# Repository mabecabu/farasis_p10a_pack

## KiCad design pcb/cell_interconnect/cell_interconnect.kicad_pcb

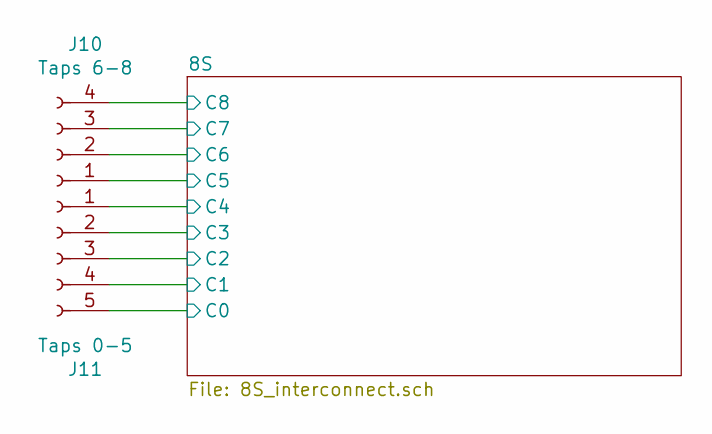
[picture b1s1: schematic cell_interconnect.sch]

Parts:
J10: Taps 6-8; PinSocket_1x04_P2.54mm_Vertical
J11: Taps 0-5; PinSocket_1x05_P2.54mm_Vertical

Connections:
/8S/C0: J11.5; also elsewhere on the board
/8S/C1: J11.4; also elsewhere on the board
/8S/C2: J11.3; also elsewhere on the board
/8S/C3: J11.2; also elsewhere on the board
/8S/C4: J11.1; also elsewhere on the board
/8S/C5: J10.1; also elsewhere on the board
/8S/C6: J10.2; also elsewhere on the board
/8S/C7: J10.3; also elsewhere on the board
/8S/C8: J10.4; also elsewhere on the board

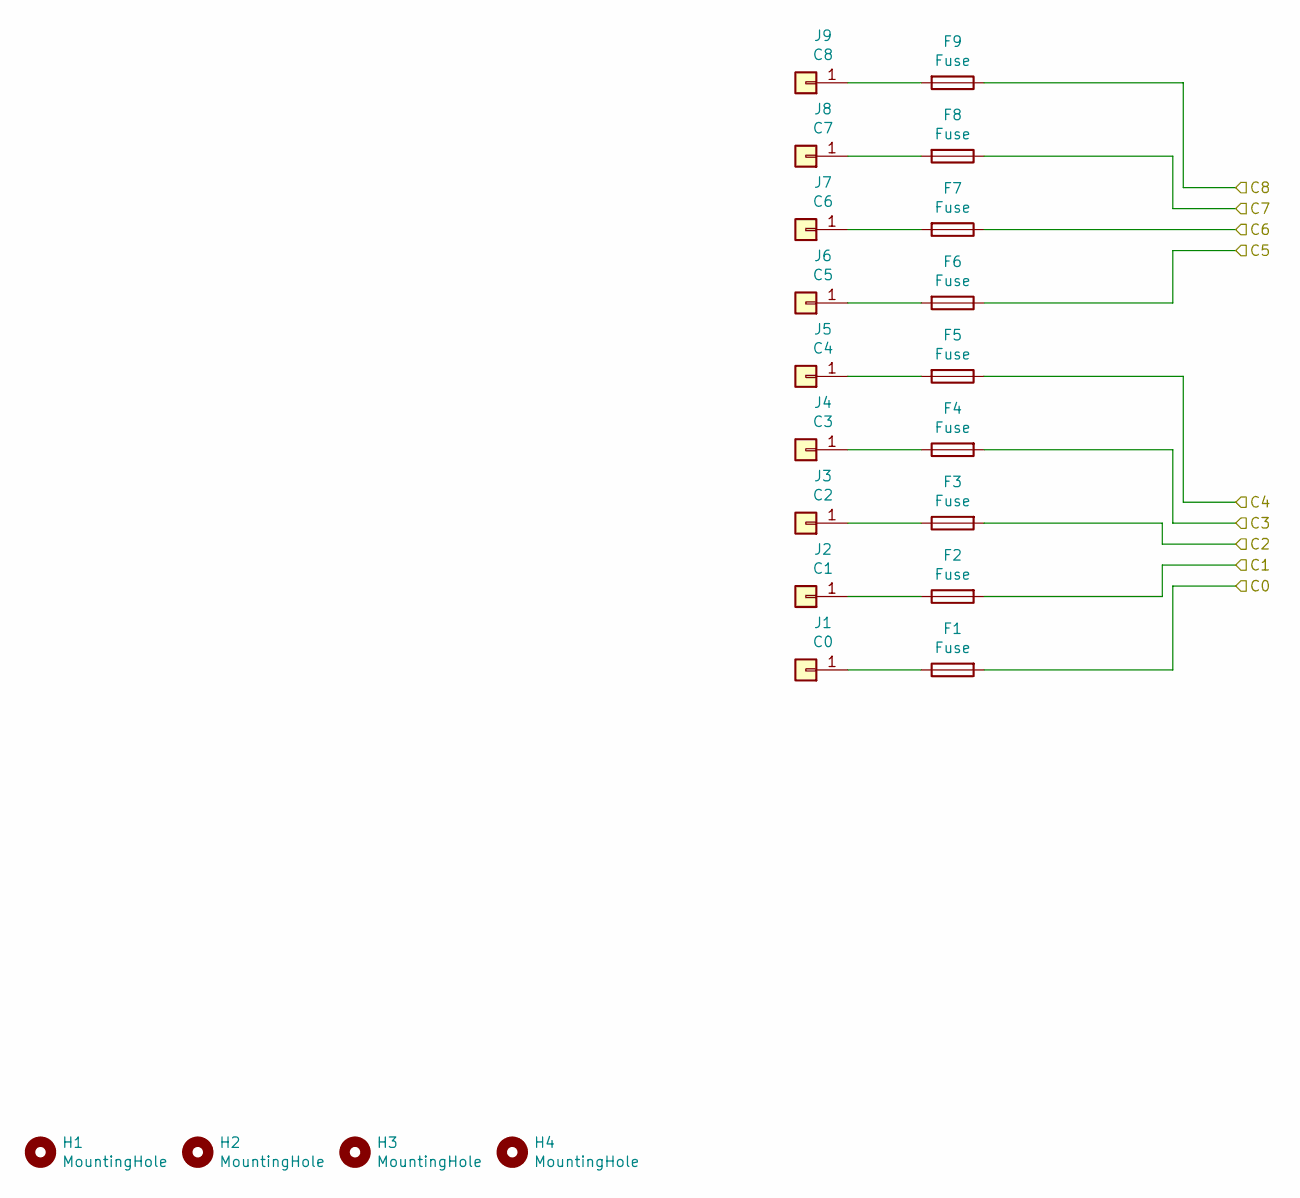
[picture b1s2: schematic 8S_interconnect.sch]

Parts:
F1, F2, F3, F4, F5, F6, F7, F9: Fuse; R_0603_1608Metric
F8: Fuse; R_0603_1608Metric; MPN C2Q 300
H1, H2, H3, H4: MountingHole; MountingHole_3.2mm_M3
J1: C0; farasis_p10a_end_tab_offset_right
J2: C1; farasis_p10a_tab
J3: C2; farasis_p10a_tab
J4: C3; farasis_p10a_tab
J5: C4; farasis_p10a_tab
J6: C5; farasis_p10a_tab
J7: C6; farasis_p10a_tab
J8: C7; farasis_p10a_tab
J9: C8; farasis_p10a_end_tab_offset_left

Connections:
/8S/C0: F1.2; also elsewhere on the board
/8S/C1: F2.2; also elsewhere on the board
/8S/C2: F3.2; also elsewhere on the board
/8S/C3: F4.2; also elsewhere on the board
/8S/C4: F5.1; also elsewhere on the board
/8S/C5: F6.1; also elsewhere on the board
/8S/C6: F7.1; also elsewhere on the board
/8S/C7: F8.1; also elsewhere on the board
/8S/C8: F9.1; also elsewhere on the board
unnamed: F1.1, J1.1
unnamed: F2.1, J2.1
unnamed: F3.1, J3.1
unnamed: F4.1, J4.1
unnamed: F5.2, J5.1
unnamed: F6.2, J6.1
unnamed: F7.2, J7.1
unnamed: F8.2, J8.1
unnamed: F9.2, J9.1

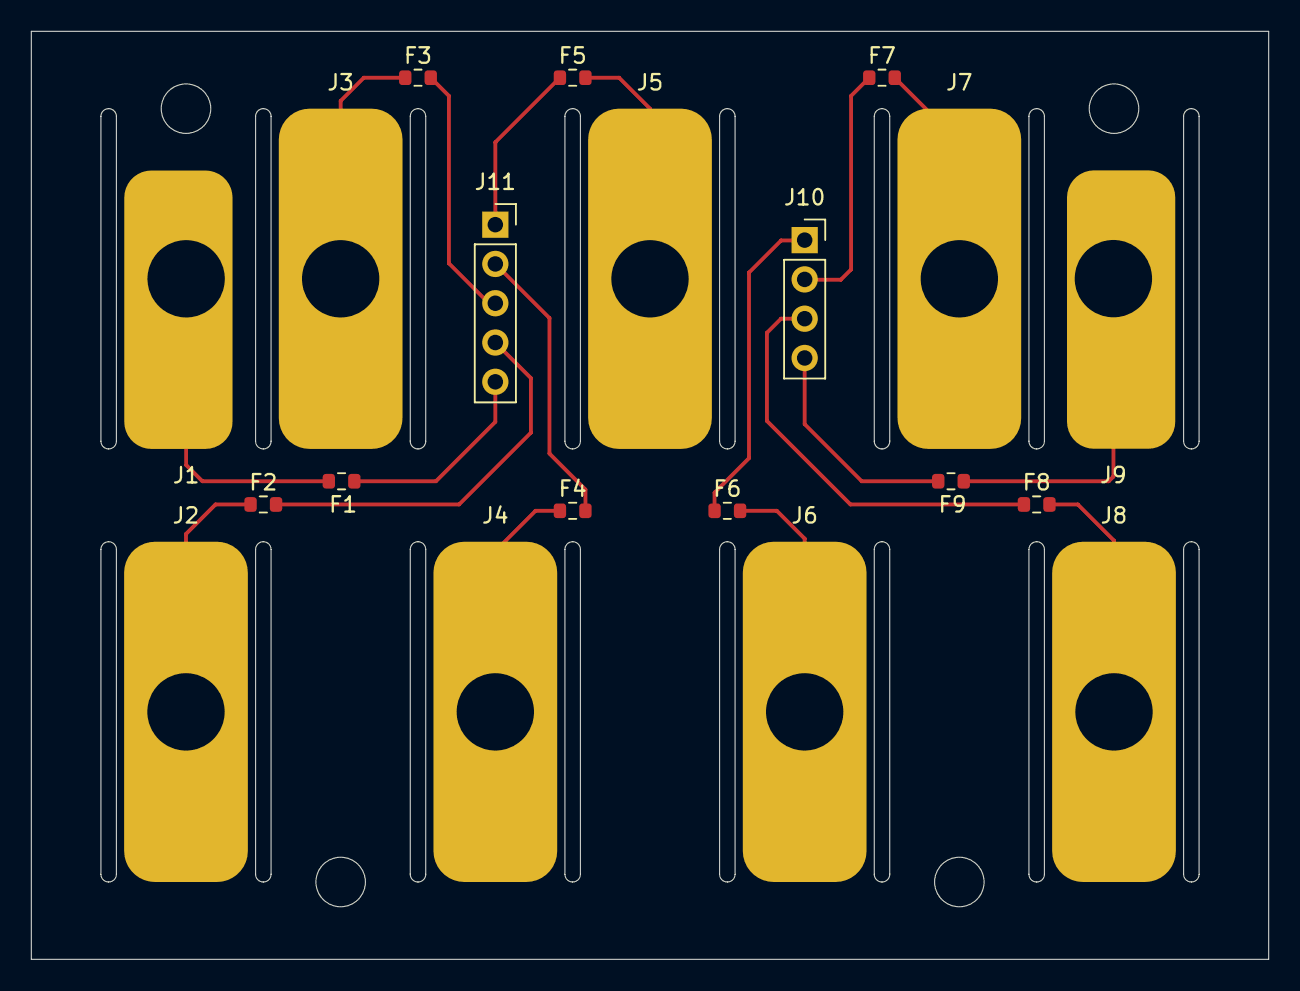
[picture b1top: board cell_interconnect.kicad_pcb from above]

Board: 2 copper layers, 80.0 x 60.0 mm, 24 parts (0 on the bottom side), 18 nets.

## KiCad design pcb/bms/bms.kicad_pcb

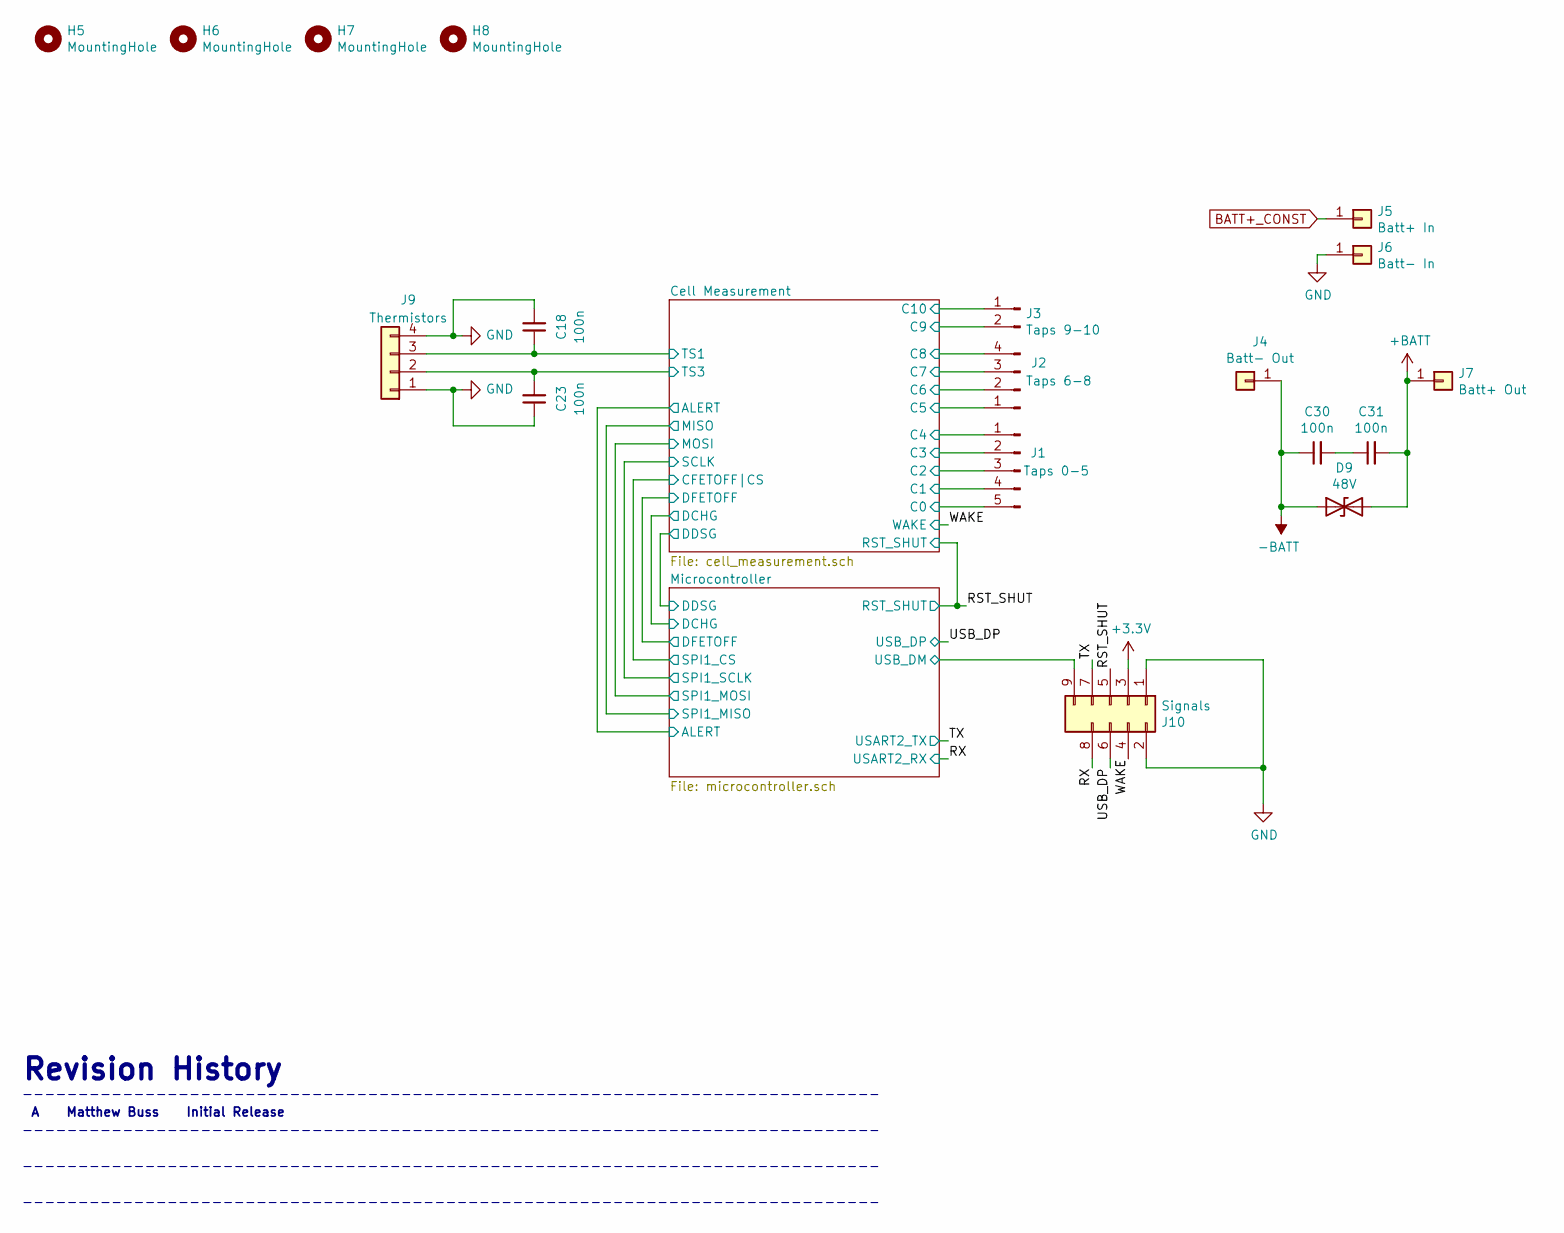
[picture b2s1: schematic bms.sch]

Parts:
C18, C23, C30, C31: 100n; C_0805_2012Metric; MPN CL21B104KCFSFNE
D9: 48V; D_SMB; MPN SMBJ48A
H5, H6, H7, H8: MountingHole; MountingHole_3.2mm_M3
J1: Taps 0-5; PinHeader_1x05_P2.54mm_Vertical
J2: Taps 6-8; PinHeader_1x04_P2.54mm_Vertical
J3: Taps 9-10; PinHeader_1x02_P2.54mm_Vertical
J4: Batt- Out; 74651195R; MPN 74651195R
J5: Batt+ In; 74651195R; MPN 74651195R
J6: Batt- In; 74651195R; MPN 74651195R
J7: Batt+ Out; 74651195R; MPN 74651195R
J9: Thermistors; JST_NSH_SM04B-NSHSS-TB_1x04-1MP_P1.00mm_Vertical; MPN SM04B-NSHSS-TB (LF)(SN)
J10: Signals; Hirose_DF62WZ-9P-2.2DSA; MPN DF62WZ-9P-2.2DSA(50)

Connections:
+3V3: J10.3; also elsewhere on the board
+BATT: C31.2, D9.2 (A2), J7.1; also elsewhere on the board
-BATT: C30.1, D9.1 (A1), J4.1; also elsewhere on the board
/Cell Measurement/C0: J1.5; also elsewhere on the board
/Cell Measurement/C1: J1.4; also elsewhere on the board
/Cell Measurement/C2: J1.3; also elsewhere on the board
/Cell Measurement/C3: J1.2; also elsewhere on the board
/Cell Measurement/C4: J1.1; also elsewhere on the board
/Cell Measurement/C5: J2.1; also elsewhere on the board
/Cell Measurement/C6: J2.2; also elsewhere on the board
/Cell Measurement/C7: J2.3; also elsewhere on the board
/Cell Measurement/C8: J2.4; also elsewhere on the board
/Cell Measurement/C9: J3.2; also elsewhere on the board
/Cell Measurement/C10: J3.1; also elsewhere on the board
/Cell Measurement/TS1: C18.1, J9.3; also elsewhere on the board
/Cell Measurement/TS3: C23.2, J9.2; also elsewhere on the board
/Microcontroller/USB_DM: J10.9; also elsewhere on the board
/RST_SHUT: J10.5; also elsewhere on the board
/RX: J10.8; also elsewhere on the board
/TX: J10.7; also elsewhere on the board
/USB_DP: J10.6; also elsewhere on the board
/WAKE: J10.4; also elsewhere on the board
BATT+_CONST: J5.1; also elsewhere on the board
GND: C18.2, C23.1, J6.1, J9.1, J9.4, J10.1, J10.2; also elsewhere on the board
unnamed: C30.2, C31.1

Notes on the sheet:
Revision History
-----------------------------------------------------------------------------
A Matthew Buss Initial Release

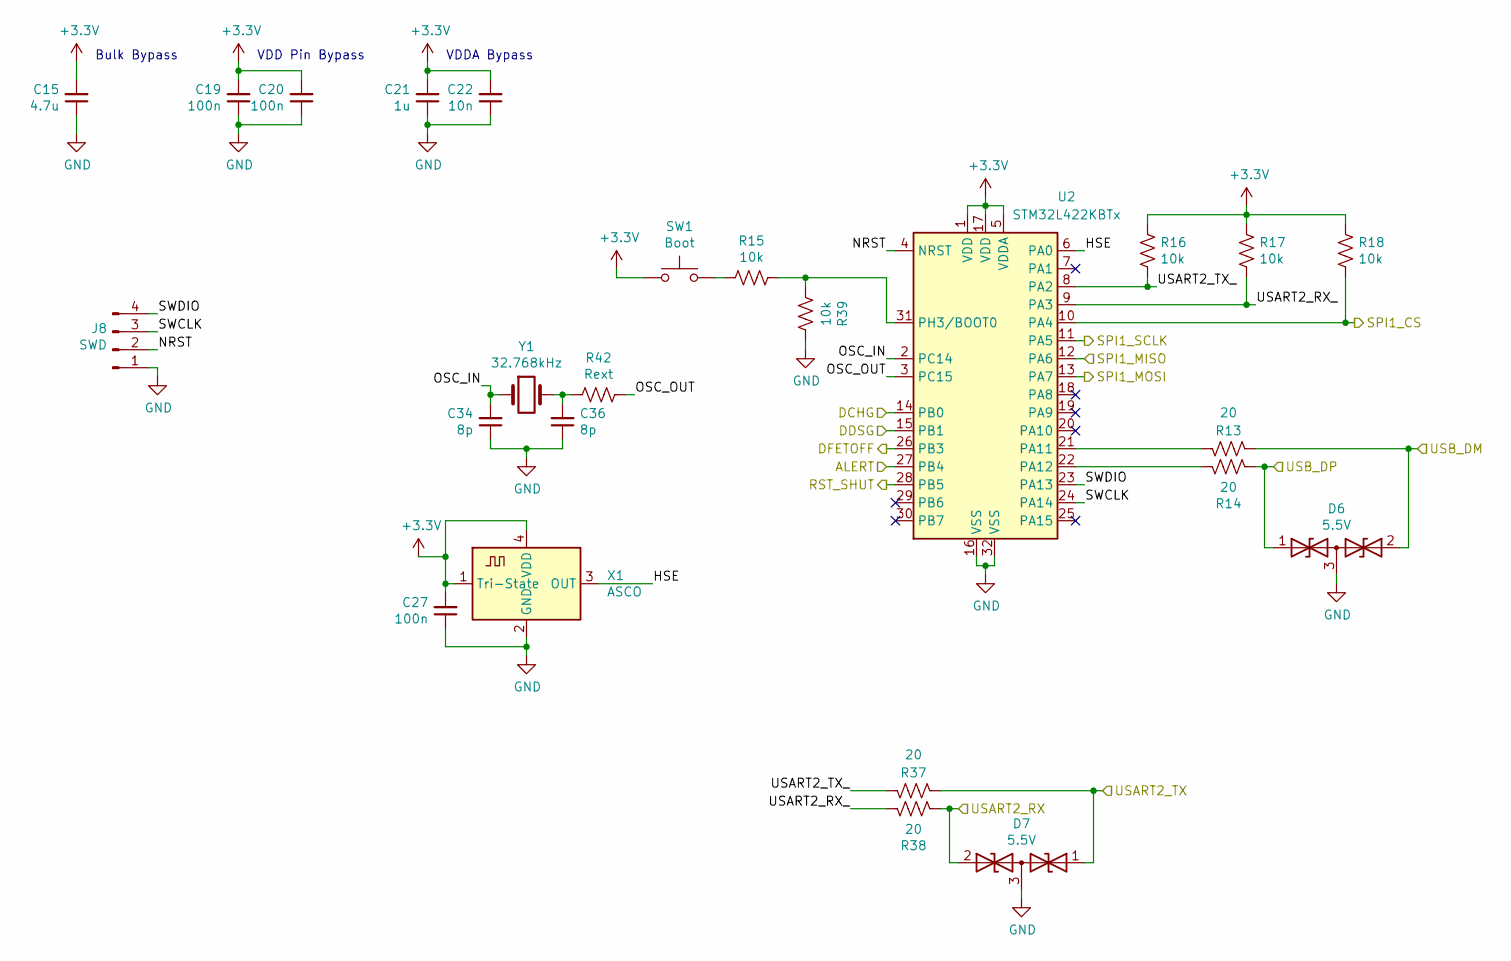
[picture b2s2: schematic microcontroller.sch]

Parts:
C15: 4.7u; C_0805_2012Metric; MPN CL21A475KOCLRNC
C19, C20, C27: 100n; C_0805_2012Metric; MPN CL21B104KCFSFNE
C21: 1u; C_0805_2012Metric; MPN CL21B105KBFNNNG
C22: 10n; C_0805_2012Metric; MPN CL21B103KBANNNC
C34, C36: 8p; C_0805_2012Metric; MPN CC0805CRNPO9BN8R0
D6, D7: 5.5V; SOT-23; MPN TPD2E2U06QDBZRQ1
J8: SWD; PinHeader_1x04_P2.54mm_Horizontal; MPN PH1RB-04-UA
R13, R14, R37, R38: 20; R_0805_2012Metric; MPN RMCF0805FT20R0
R15, R16, R17, R18, R39: 10k; R_0805_2012Metric; MPN RMCF0805FT10K0
R42: Rext; R_0805_2012Metric
SW1: Boot; SW_SPST_PTS645; MPN PTS645SK50SMTR92 LFS
U2: STM32L422KBTx; LQFP-32_7x7mm_P0.8mm; MPN STM32L422KBT6
X1: ASCO; Oscillator_SMD_Abracon_ASCO-4Pin_1.6x1.2mm; MPN ASCO-8.000MHZ-EK-T3
Y1: 32.768kHz; Crystal_SMD_MicroCrystal_CC8V-T1A-2Pin_2.0x1.2mm_HandSolder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; MPN CM8V-T1A-32.768KHZ-9PF-20PPM-TB-QA

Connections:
+3V3: C15.2, C19.2, C20.2, C21.2, C22.2, C27.2, R16.1, R17.1, R18.1, SW1.1, U2.1 (VDD), U2.5 (VDDA), U2.17 (VDD), X1.1 (Tri-State), X1.4 (VDD); also elsewhere on the board
/Cell Measurement/ALERT: U2.27 (PB4); also elsewhere on the board
/Cell Measurement/CFETOFF|CS: R18.2, U2.10 (PA4); also elsewhere on the board
/Cell Measurement/DCHG: U2.14 (PB0); also elsewhere on the board
/Cell Measurement/DDSG: U2.15 (PB1); also elsewhere on the board
/Cell Measurement/DFETOFF: U2.26 (PB3); also elsewhere on the board
/Cell Measurement/MISO: U2.12 (PA6); also elsewhere on the board
/Cell Measurement/MOSI: U2.13 (PA7); also elsewhere on the board
/Cell Measurement/SCLK: U2.11 (PA5); also elsewhere on the board
/Microcontroller/HSE: U2.6 (PA0), X1.3 (OUT)
/Microcontroller/NRST: J8.2, U2.4 (NRST)
/Microcontroller/OSC_IN: C34.2, U2.2 (PC14), Y1.1
/Microcontroller/OSC_OUT: R42.1, U2.3 (PC15)
/Microcontroller/SWCLK: J8.3, U2.24 (PA14)
/Microcontroller/SWDIO: J8.4, U2.23 (PA13)
/Microcontroller/USART2_RX_: R17.2, R38.2, U2.9 (PA3)
/Microcontroller/USART2_TX_: R16.2, R37.2, U2.8 (PA2)
/Microcontroller/USB_DM: D6.2 (A2), R13.1; also elsewhere on the board
/RST_SHUT: U2.28 (PB5); also elsewhere on the board
/RX: D7.2 (A2), R38.1; also elsewhere on the board
/TX: D7.1 (A1), R37.1; also elsewhere on the board
/USB_DP: D6.1 (A1), R14.1; also elsewhere on the board
GND: C15.1, C19.1, C20.1, C21.1, C22.1, C27.1, C34.1, C36.1, D6.3 (common), D7.3 (common), J8.1, R39.1, U2.16 (VSS), U2.32 (VSS), X1.2 (GND); also elsewhere on the board
unnamed: C36.2, R42.2, Y1.2
unnamed: R13.2, U2.21 (PA11)
unnamed: R14.2, U2.22 (PA12)
unnamed: R15.1, R39.2, U2.31 (PH3/BOOT0)
unnamed: R15.2, SW1.2

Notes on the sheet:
Bulk Bypass
VDD Pin Bypass
VDDA Bypass

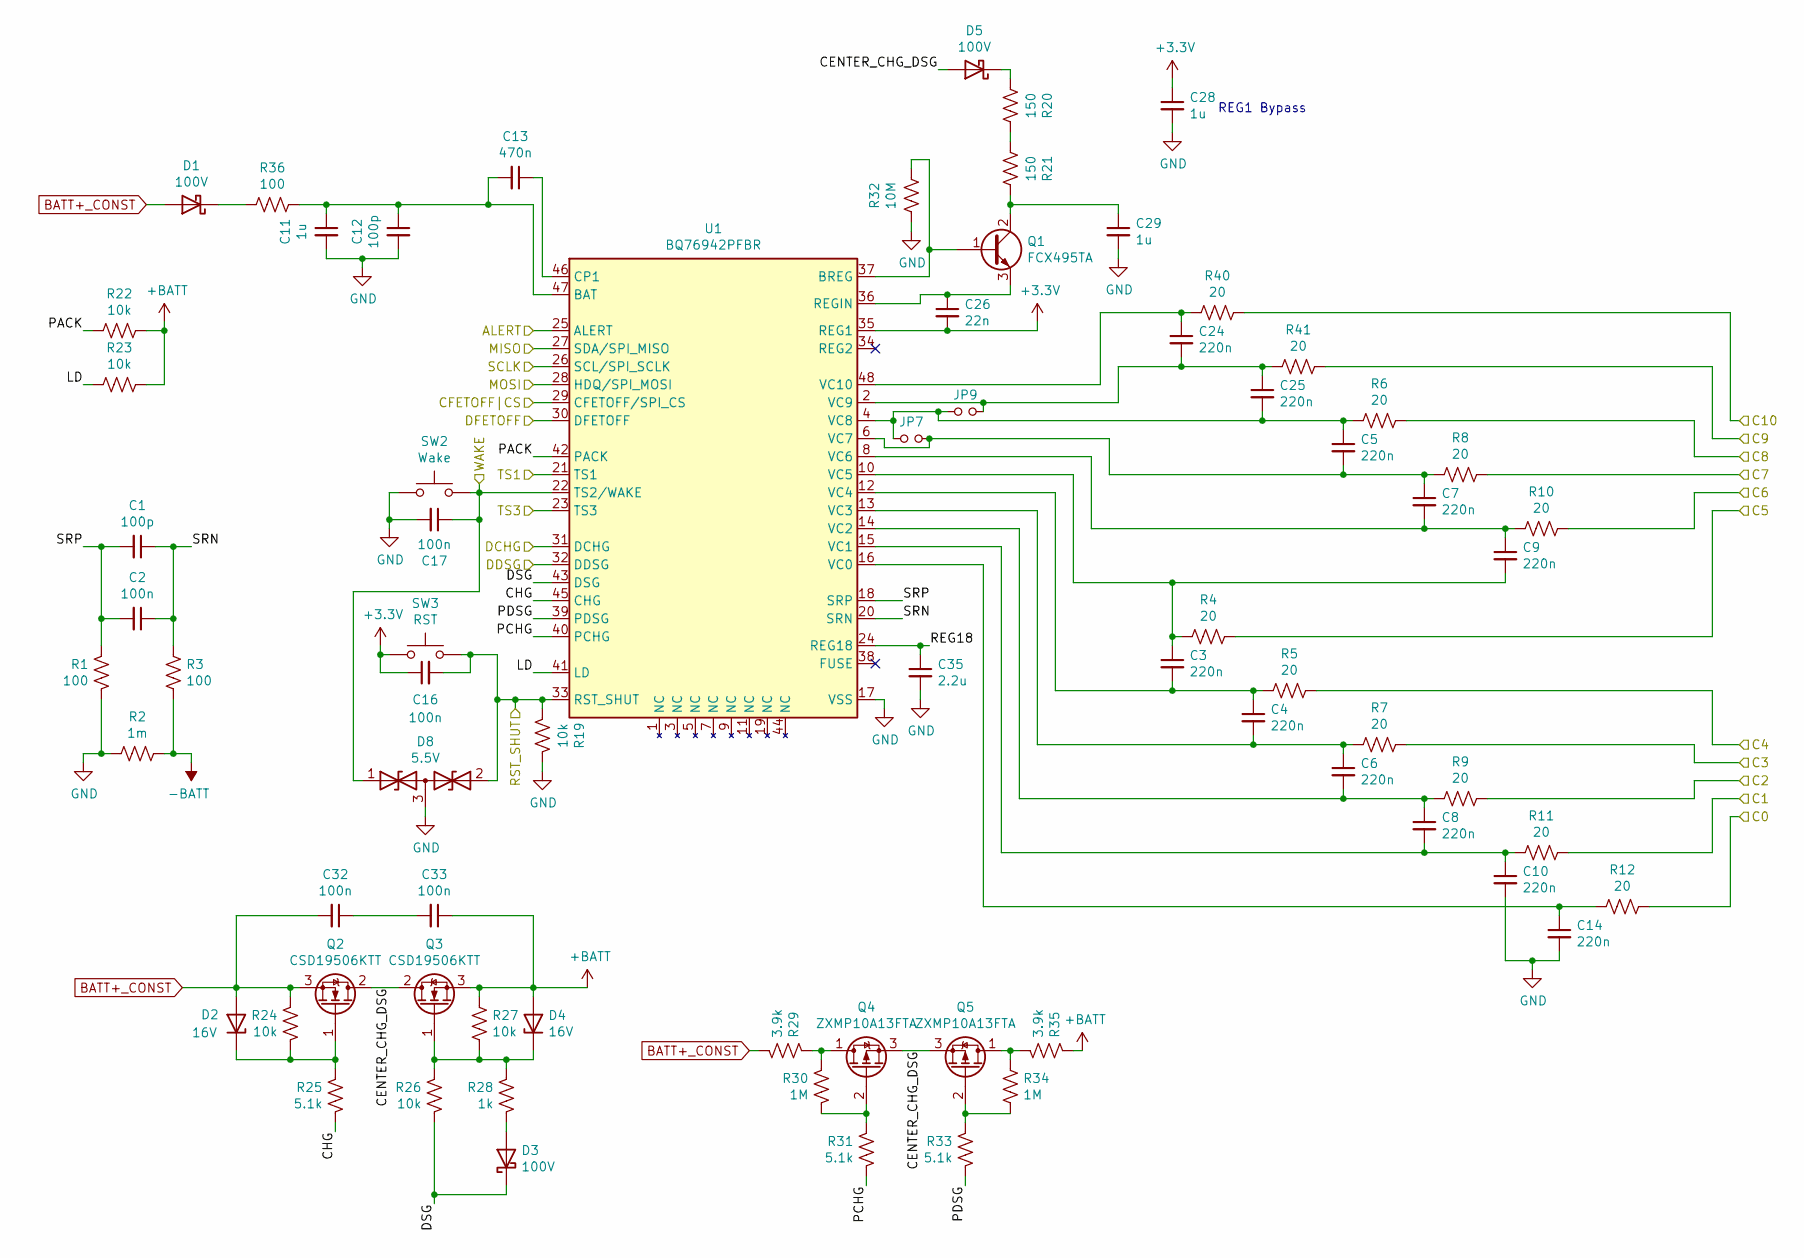
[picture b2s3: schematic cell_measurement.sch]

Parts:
C1, C12: 100p; C_0805_2012Metric; MPN C0805C101J1GACTU
C2, C16, C17, C32, C33: 100n; C_0805_2012Metric; MPN CL21B104KCFSFNE
C3, C4, C5, C6, C7, C8, C9, C10, C14, C24, C25: 220n; C_0805_2012Metric; MPN C0805C224K1RECAUTO
C11, C28, C29: 1u; C_0805_2012Metric; MPN CL21B105KBFNNNG
C13: 470n; C_0805_2012Metric; MPN CL21B473KCCWPNC
C26: 22n; C_0805_2012Metric; MPN CL21B223KBANFNC
C35: 2.2u; C_0805_2012Metric; MPN CL21B225KPFNNNE
D1, D3, D5: 100V; D_SOD-123; MPN BAT46W-7-F
D2, D4: 16V; D_SOD-123; MPN MMSZ5246B-7-F
D8: 5.5V; SOT-23; MPN TPD2E2U06QDBZRQ1
JP7, JP9: Jumper_NO_Small; SolderJumper-2_P1.3mm_Open_RoundedPad1.0x1.5mm
Q1: FCX495TA; SOT-89-3; MPN FCX495TA
Q2, Q3: CSD19506KTT; TO-263-2; MPN CSD19506KTT
Q4, Q5: ZXMP10A13FTA; SOT-23; MPN ZXMP10A13FTA
R1, R3, R36: 100; R_0805_2012Metric; MPN CR0805-FX-1000ELF
R2: 1m; R_2512_6332Metric; MPN CSR2512C0R001F
R4, R5, R6, R7, R8, R9, R10, R11, R12, R40, R41: 20; R_0805_2012Metric; MPN RMCF0805FT20R0
R19, R22, R23, R24, R26, R27: 10k; R_0805_2012Metric; MPN RMCF0805FT10K0
R20, R21: 150; R_0805_2012Metric; MPN RMCF0805FT150R
R25, R31, R33: 5.1k; R_0805_2012Metric; MPN RMCF0805FT5K10
R28: 1k; R_0805_2012Metric; MPN CR0805-FX-1001ELF
R29, R35: 3.9k; R_0805_2012Metric; MPN RMCF0805FT3K90
R30, R34: 1M; R_0805_2012Metric; MPN RMCF0805FT1M00
R32: 10M; R_0805_2012Metric; MPN RMCF0805FT10M0
SW2: Wake; SW_SPST_PTS645; MPN PTS645SK50SMTR92 LFS
SW3: RST; SW_SPST_PTS645; MPN PTS645SK50SMTR92 LFS
U1: BQ76942PFBR; LQFP-48_7x7mm_P0.5mm; MPN BQ7694201PFBR

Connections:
+3V3: C16.1, C26.2, C28.1, SW3.1, U1.35 (REG1); also elsewhere on the board
+BATT: C33.1, D4.2 (A), Q3.3 (S), R22.1, R23.1, R27.2, R35.2; also elsewhere on the board
-BATT: R2.1, R3.2; also elsewhere on the board
/Cell Measurement/ALERT: U1.25 (ALERT); also elsewhere on the board
/Cell Measurement/C0: R12.1; also elsewhere on the board
/Cell Measurement/C1: R11.1; also elsewhere on the board
/Cell Measurement/C2: R9.1; also elsewhere on the board
/Cell Measurement/C3: R7.1; also elsewhere on the board
/Cell Measurement/C4: R5.1; also elsewhere on the board
/Cell Measurement/C5: R4.1; also elsewhere on the board
/Cell Measurement/C6: R10.1; also elsewhere on the board
/Cell Measurement/C7: R8.1; also elsewhere on the board
/Cell Measurement/C8: R6.1; also elsewhere on the board
/Cell Measurement/C9: R41.1; also elsewhere on the board
/Cell Measurement/C10: R40.1; also elsewhere on the board
/Cell Measurement/CENTER_CHG_DSG: D5.2 (A), Q2.2 (D), Q3.2 (D), Q4.3 (S), Q5.3 (S)
/Cell Measurement/CFETOFF|CS: U1.29 (CFETOFF/SPI_CS); also elsewhere on the board
/Cell Measurement/CHG: R25.1, U1.45 (CHG)
/Cell Measurement/DCHG: U1.31 (DCHG); also elsewhere on the board
/Cell Measurement/DDSG: U1.32 (DDSG); also elsewhere on the board
/Cell Measurement/DFETOFF: U1.30 (DFETOFF); also elsewhere on the board
/Cell Measurement/DSG: D3.1 (K), R26.1, U1.43 (DSG)
/Cell Measurement/LD: R23.2, U1.41 (LD)
/Cell Measurement/MISO: U1.27 (SDA/SPI_MISO); also elsewhere on the board
/Cell Measurement/MOSI: U1.28 (HDQ/SPI_MOSI); also elsewhere on the board
/Cell Measurement/PACK: R22.2, U1.42 (PACK)
/Cell Measurement/PCHG: R31.1, U1.40 (PCHG)
/Cell Measurement/PDSG: R33.1, U1.39 (PDSG)
/Cell Measurement/REG18: C35.1, U1.24 (REG18)
/Cell Measurement/SCLK: U1.26 (SCL/SPI_SCLK); also elsewhere on the board
/Cell Measurement/SRN: C1.1, C2.1, R3.1, U1.20 (SRN)
/Cell Measurement/SRP: C1.2, C2.2, R1.2, U1.18 (SRP)
/Cell Measurement/TS1: U1.21 (TS1); also elsewhere on the board
/Cell Measurement/TS3: U1.23 (TS3); also elsewhere on the board
/RST_SHUT: C16.2, D8.2 (A2), R19.1, SW3.2, U1.33 (RST_SHUT); also elsewhere on the board
/WAKE: C17.1, D8.1 (A1), SW2.2, U1.22 (TS2/WAKE); also elsewhere on the board
BATT+_CONST: C32.2, D1.2 (A), D2.2 (A), Q2.3 (S), R24.2, R29.1; also elsewhere on the board
GND: C10.2, C11.2, C12.2, C14.2, C17.2, C28.2, C29.2, C35.2, D8.3 (common), R1.1, R2.2, R19.2, R32.2, SW2.1, U1.17 (VSS); also elsewhere on the board
unnamed: C3.1, C9.2, R4.2, U1.10 (VC5)
unnamed: C3.2, C4.1, R5.2, U1.12 (VC4)
unnamed: C4.2, C6.1, R7.2, U1.13 (VC3)
unnamed: C5.2, C7.1, JP7.2, R8.2, U1.6 (VC7)
unnamed: C6.2, C8.1, R9.2, U1.14 (VC2)
unnamed: C7.2, C9.1, R10.2, U1.8 (VC6)
unnamed: C8.2, C10.1, R11.2, U1.15 (VC1)
unnamed: C11.1, C12.1, C13.2, R36.1, U1.47 (BAT)
unnamed: C13.1, U1.46 (CP1)
unnamed: C14.1, R12.2, U1.16 (VC0)
unnamed: C24.1, R40.2, U1.48 (VC10)
unnamed: C24.2, C25.1, JP9.2, R41.2, U1.2 (VC9)
unnamed: C5.1, C25.2, JP7.1, JP9.1, R6.2, U1.4 (VC8)
unnamed: C26.1, Q1.3 (E), U1.36 (REGIN)
unnamed: C29.1, Q1.2 (C), R21.1
unnamed: C32.1, C33.2
unnamed: D1.1 (K), R36.2
unnamed: D2.1 (K), Q2.1 (G), R24.1, R25.2
unnamed: D3.2 (A), R28.1
unnamed: D4.1 (K), Q3.1 (G), R26.2, R27.1, R28.2
unnamed: D5.1 (K), R20.2
unnamed: Q1.1 (B), R32.1, U1.37 (BREG)
unnamed: Q4.1 (D), R29.2, R30.2
unnamed: Q4.2 (G), R30.1, R31.2
unnamed: Q5.1 (D), R34.2, R35.1
unnamed: Q5.2 (G), R33.2, R34.1
unnamed: R20.1, R21.2

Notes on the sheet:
REG1 Bypass

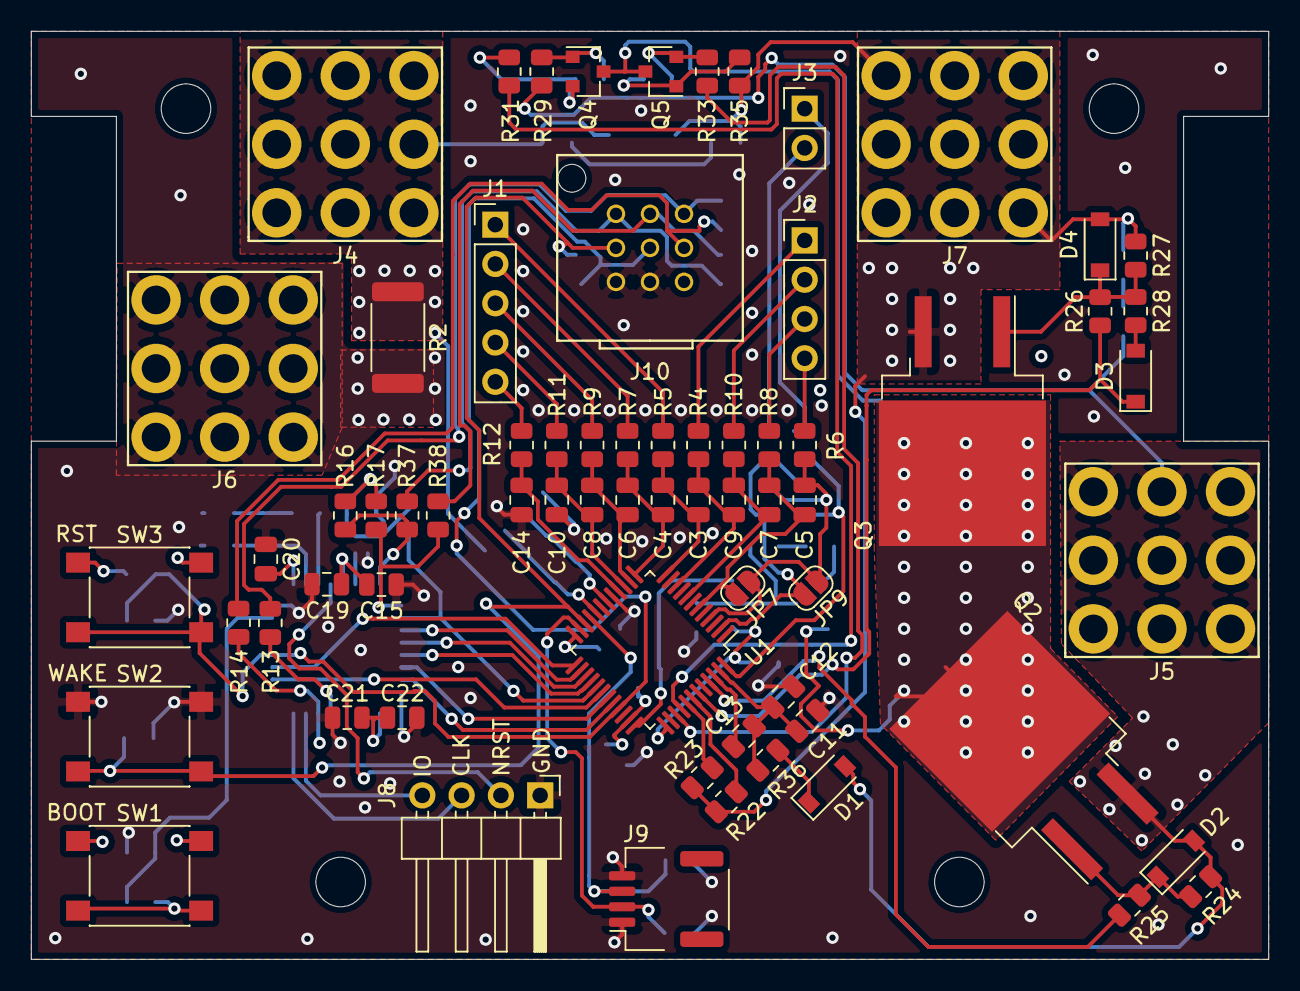
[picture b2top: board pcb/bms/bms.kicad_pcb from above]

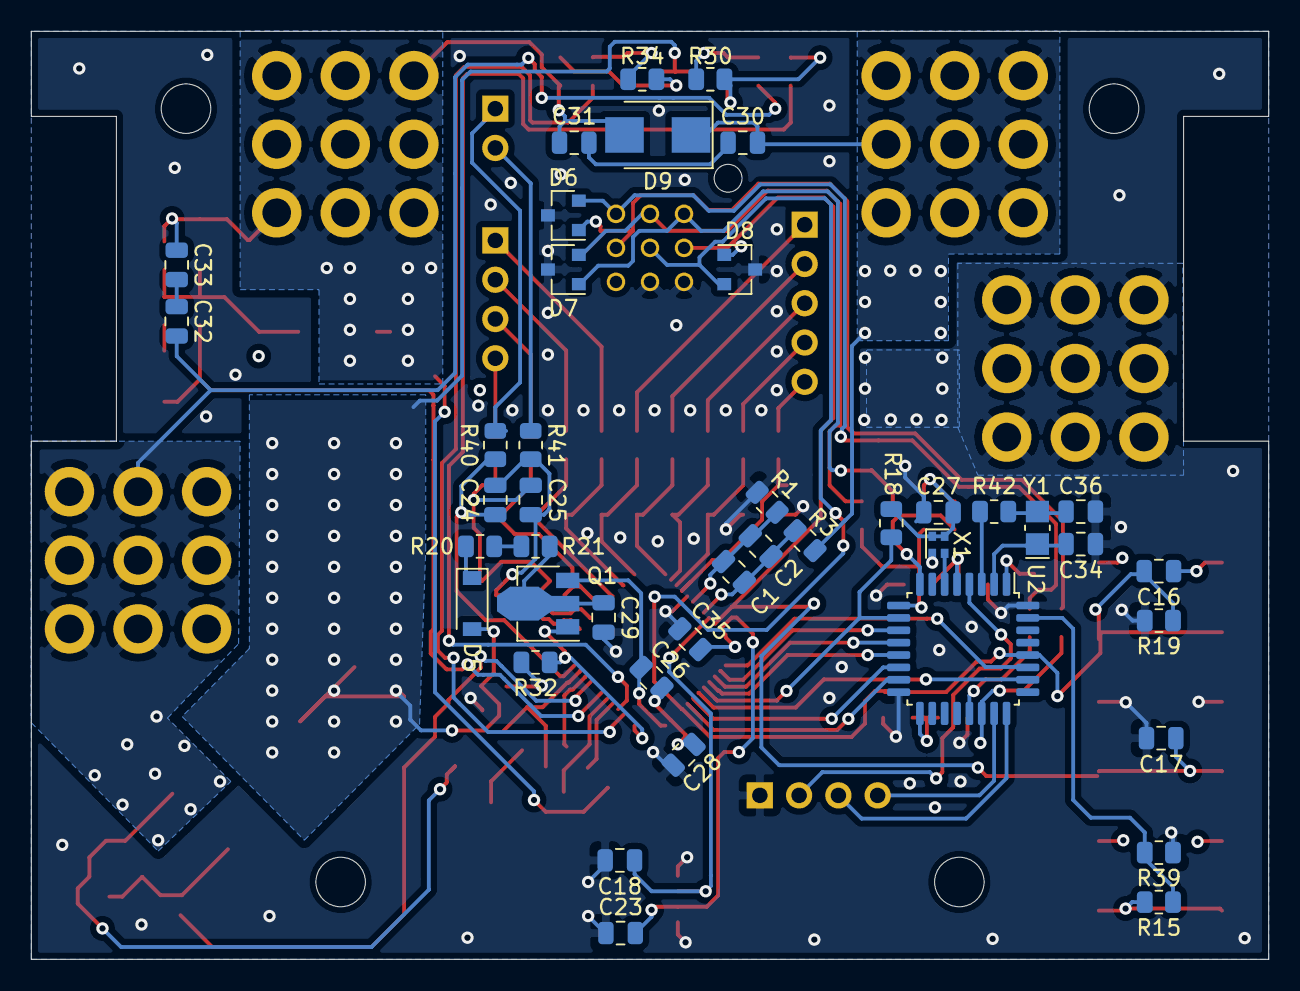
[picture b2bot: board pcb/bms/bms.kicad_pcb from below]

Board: 4 copper layers, 80.0 x 60.0 mm, 115 parts (42 on the bottom side), 83 nets.

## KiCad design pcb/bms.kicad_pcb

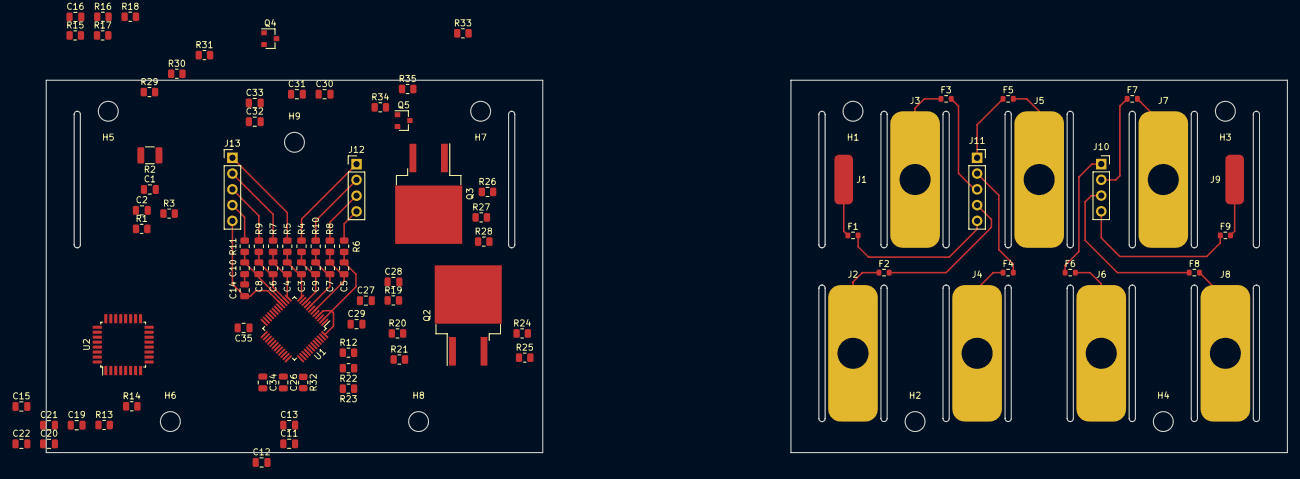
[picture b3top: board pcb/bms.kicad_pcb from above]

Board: 2 copper layers, 200.0 x 60.0 mm, 102 parts (0 on the bottom side), 79 nets.

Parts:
C1, C12: 100p; C_0805_2012Metric
C2, C19, C20, C30, C31, C32, C33, C34: 0.1u; C_0805_2012Metric
C3, C4, C5, C6, C7, C8, C9, C10, C14: 220n; C_0805_2012Metric
C11, C21, C27, C28, C29: 1u; C_0805_2012Metric
C13: 0.47u; C_0805_2012Metric
C15: 4.7u; C_0805_2012Metric
C16: 100n; C_0805_2012Metric
C22: 10n; C_0805_2012Metric
C26: 22n; C_0805_2012Metric
C35: 2.2u; C_0805_2012Metric
F1, F2, F3, F4, F5, F6, F7, F8, F9: Fuse; R_0603_1608Metric
H1, H2, H3, H4, H5, H6, H7, H8, H9: MountingHole; MountingHole_3.2mm_M3
J1: C0; cell_tap_wire_land
J2: C1; farasis_p10a_tab
J3: C2; farasis_p10a_tab
J4: C3; farasis_p10a_tab
J5: C4; farasis_p10a_tab
J6: C5; farasis_p10a_tab
J7: C6; farasis_p10a_tab
J8: C7; farasis_p10a_tab
J9: C8; cell_tap_wire_land
J10: Taps 6-8; PinSocket_1x04_P2.54mm_Vertical
J11: Taps 0-5; PinSocket_1x05_P2.54mm_Vertical
J12: Taps 6-8; PinHeader_1x04_P2.54mm_Vertical
J13: Taps 0-5; PinHeader_1x05_P2.54mm_Vertical
Q2, Q3: CSD19506KTT; TO-263-2
Q4, Q5: ZXMP10A13FTA; SOT-23
R1, R3, R12: 100; R_0805_2012Metric
R2: 2m; R_1210_3225Metric
R4, R5, R6, R7, R8, R9, R10, R11: 20; R_0805_2012Metric
R13, R14: 22; R_0805_2012Metric
R15, R16, R17, R18, R19, R22, R23, R24, R26, R27: 10k; R_0805_2012Metric
R20, R21: 150; R_0805_2012Metric
R25, R31, R33: 5.1k; R_0805_2012Metric
R28: 1k; R_0805_2012Metric
R29, R35: 3.9k; R_0805_2012Metric
R30, R34: 1M; R_0805_2012Metric
R32: 10M; R_0805_2012Metric
U1: BQ76942PFBR; LQFP-48_7x7mm_P0.5mm
U2: STM32L422KBTx; LQFP-32_7x7mm_P0.8mm

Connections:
+3V3: C15.2, C19.2, C20.2, C21.2, C22.2, C26.2, C27.1, C28.1, R16.1, R17.1, R18.1, U1.34, U1.35, U2.1, U2.5, U2.17
+BATT: C31.2, C33.1, Q3.3, R22.1, R23.1, R27.2, R35.2
-BATT: C30.1, R2.1, R3.2
/Cell Interconnect/C0: F1.2, J11.5
/Cell Interconnect/C1: F2.2, J11.4
/Cell Interconnect/C2: F3.2, J11.3
/Cell Interconnect/C3: F4.2, J11.2
/Cell Interconnect/C4: F5.1, J11.1
/Cell Interconnect/C5: F6.1, J10.1
/Cell Interconnect/C6: F7.1, J10.2
/Cell Interconnect/C7: F8.1, J10.3
/Cell Interconnect/C8: F9.1, J10.4
/Cell Measurement/ALERT: U1.25, U2.27
/Cell Measurement/C0: C14.1, J13.5, U1.16
/Cell Measurement/C1: J13.4, R11.1
/Cell Measurement/C2: J13.3, R9.1
/Cell Measurement/C3: J13.2, R7.1
/Cell Measurement/C4: J13.1, R5.1
/Cell Measurement/C5: J12.1, R4.1
/Cell Measurement/C6: J12.2, R10.1
/Cell Measurement/C7: J12.3, R8.1
/Cell Measurement/C8: J12.4, R6.1
/Cell Measurement/CENTER_CHG_DSG: Q2.2, Q3.2, Q4.3, Q5.3
/Cell Measurement/CFETOFF|CS: R18.2, U1.29, U2.10
/Cell Measurement/CHG: R25.1, U1.45
/Cell Measurement/DCHG: U1.31, U2.15
/Cell Measurement/DDSG: U1.32, U2.14
/Cell Measurement/DFETOFF: U1.30, U2.26
/Cell Measurement/DSG: R26.1, U1.43
/Cell Measurement/LD: R23.2, U1.41
/Cell Measurement/MISO: U1.27, U2.12
/Cell Measurement/MOSI: U1.28, U2.13
/Cell Measurement/PACK: R22.2, U1.42
/Cell Measurement/PCHG: R31.1, U1.40
/Cell Measurement/PDSG: R33.1, U1.39
/Cell Measurement/REG18: C35.1, U1.24
/Cell Measurement/SCLK: U1.26, U2.11
/Cell Measurement/SRN: C1.1, C2.1, R3.1, U1.20
/Cell Measurement/SRP: C1.2, C2.2, R1.2, U1.18
/Microcontroller/NRST: C16.2, U2.4
/Microcontroller/USART2_RX: R17.2, U2.9
/Microcontroller/USART2_TX: R16.2, U2.8
BATT+_CONST: C32.2, Q2.3, R24.2, R29.1
GND: C10.2, C11.2, C12.2, C14.2, C15.1, C16.1, C19.1, C20.1, C21.1, C22.1, C27.2, C28.2, C29.2, C34.2, C35.2, R1.1, R2.2, R19.2, R32.2, U1.17, U2.16, U2.32
unnamed: C3.1, C9.2, R4.2, U1.10
unnamed: C3.2, C4.1, R5.2, U1.12
unnamed: C4.2, C6.1, R7.2, U1.13
unnamed: C5.1, R6.2, U1.2, U1.4, U1.48
unnamed: C5.2, C7.1, R8.2, U1.6
unnamed: C6.2, C8.1, R9.2, U1.14
unnamed: C7.2, C9.1, R10.2, U1.8
unnamed: C8.2, C10.1, R11.2, U1.15
unnamed: C11.1, C12.1, C13.2, R12.1, U1.47
unnamed: C13.1, U1.46
unnamed: C26.1, U1.36
unnamed: C29.1, R21.1
unnamed: C30.2, C31.1
unnamed: C32.1, C33.2
unnamed: C34.1, R19.1, U1.33
unnamed: Q2.1, R24.1, R25.2
unnamed: Q3.1, R26.2, R27.1, R28.2
unnamed: F1.1, J1.1
unnamed: F2.1, J2.1
unnamed: F3.1, J3.1
unnamed: F4.1, J4.1
unnamed: F5.2, J5.1
unnamed: F6.2, J6.1
unnamed: F7.2, J7.1
unnamed: F8.2, J8.1
unnamed: F9.2, J9.1
unnamed: R32.1, U1.37
unnamed: Q4.1, R29.2, R30.2
unnamed: Q4.2, R30.1, R31.2
unnamed: Q5.1, R34.2, R35.1
unnamed: Q5.2, R33.2, R34.1
unnamed: R13.2, U2.21
unnamed: R14.2, U2.22
unnamed: R15.1, U2.31
unnamed: R20.1, R21.2

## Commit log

2021-02-10 add datasheets, start schematic capture
2021-04-21 finished cell tab board
2021-04-24 AFE mostly complete
2021-05-02 connectors, microcontroller
2021-05-07 microcontroller added
2021-05-07 split boards to two separate projects
2021-05-12 pretty much ready to go
2021-05-13 rev1 as manufactured
